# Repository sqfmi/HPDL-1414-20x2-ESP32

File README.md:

# HPDL-1414-20x2-ESP32
- 20x2 Character Display with HPDL1414 modules &amp; ESP32
- PCB Structure
- Arduino Library 👉 https://github.com/sqfmi/HPDL1414-74HC595-Arduino
- OSHWA Certified [**US000625**](https://certification.oshwa.org/us000625.html)

## Bill of Materials
| Component           | Quantity | Link                                             |
|---------------------|----------|--------------------------------------------------|
| HPDL1414            | 10       | https://www.aliexpress.com/item/32604004029.html |
| ESP32-WROOM-32D     | 1        |                                                  |
| CP2104              | 1        |                                                  |
| AMS1117-3.3V        | 1        |                                                  |
| 74HC595 SOIC-16     | 3        |                                                  |
| 0.1uF 0805          | 15       |                                                  |
| 4.7uF 0805          | 1        |                                                  |
| 10uF 0805           | 1        |                                                  |
| Micro USB Connector | 1        |                                                  |
| S8050 SOT-23        | 2        |                                                  |
| 10K 0805            | 4        |                                                  |

## License
Designed by SQFMI. Creative Commons Attribution/Share-Alike. See LICENSE for additional information.

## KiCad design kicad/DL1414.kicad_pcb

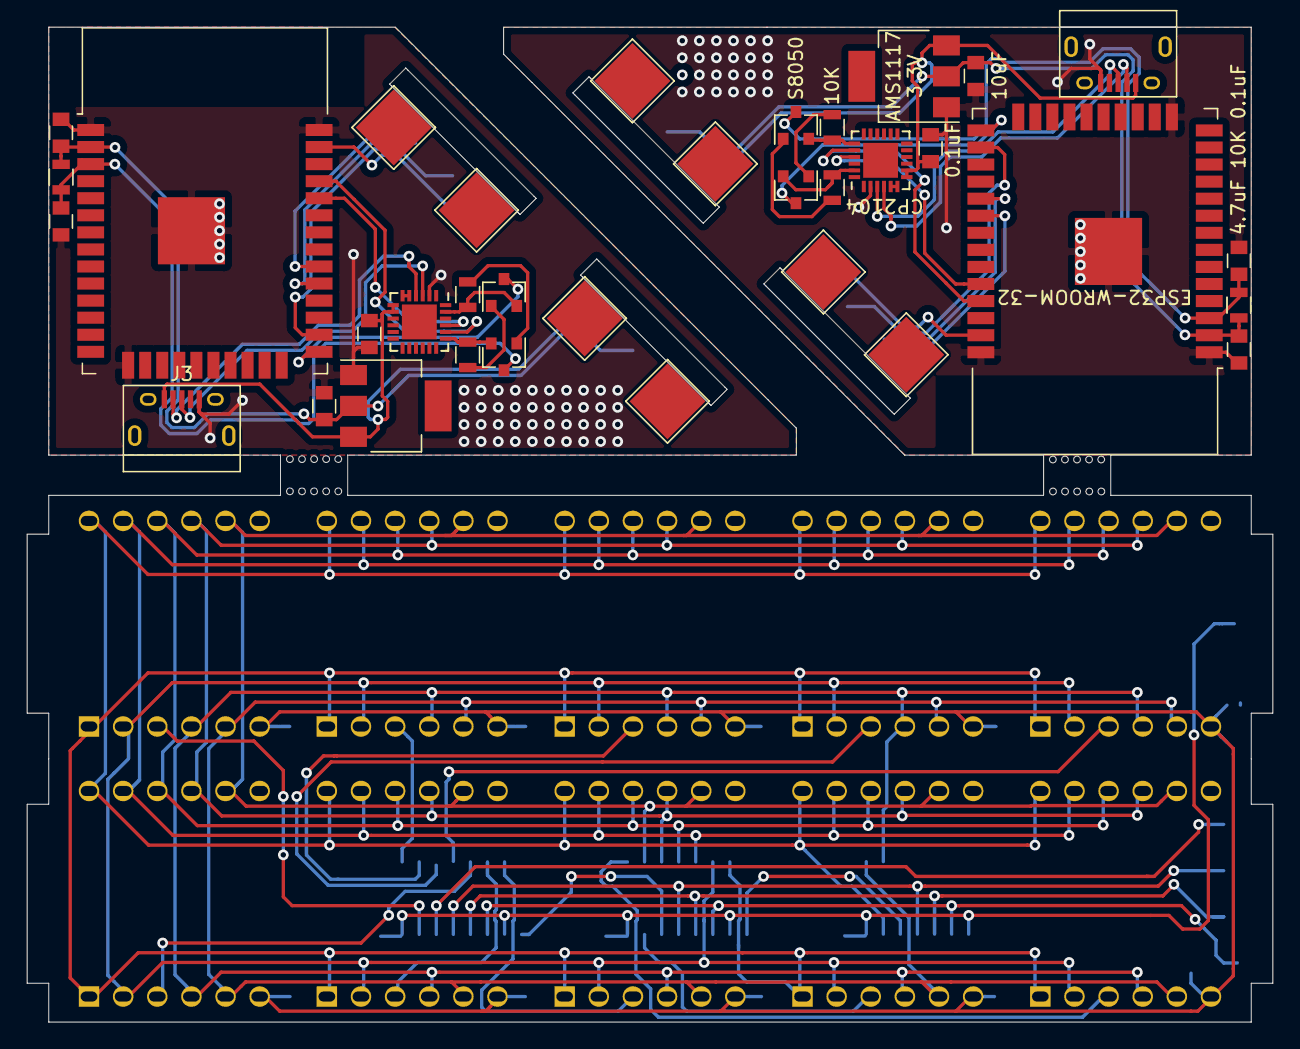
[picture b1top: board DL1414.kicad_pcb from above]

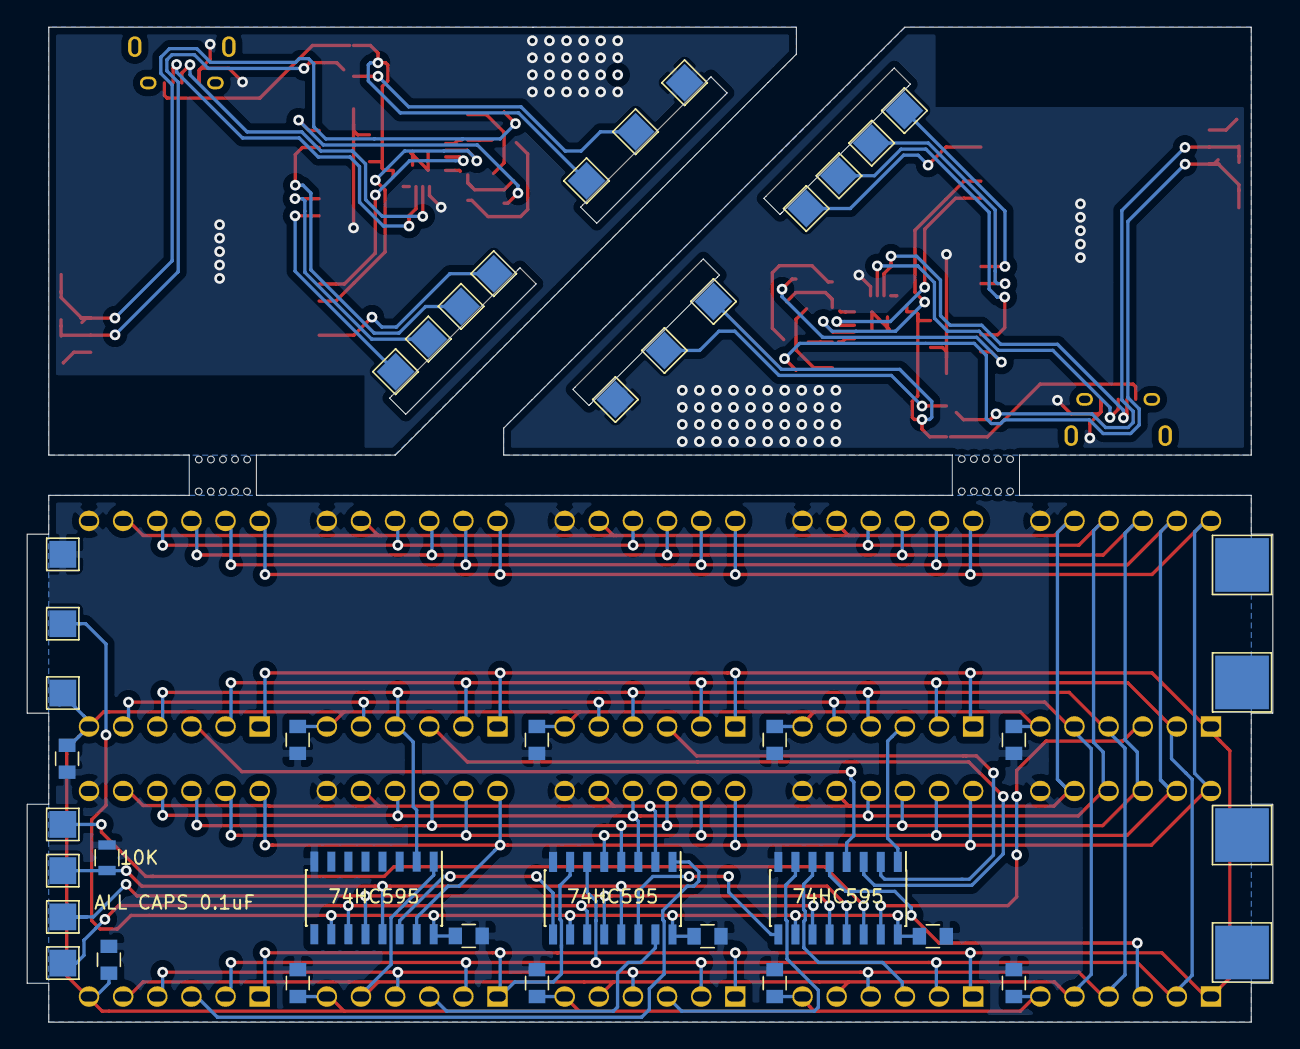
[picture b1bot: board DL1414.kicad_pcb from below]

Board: 2 copper layers, 92.7 x 74.0 mm, 86 parts (42 on the bottom side), 84 nets.

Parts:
C1, C2, C3, C4, C5, C6, C7, C8, C9, C10, C12, C12#2, C13, C13#2, C14, C15, C16: 0.1uF; C_0805
C11, C11#2: 4.7uF; C_0805
C17, C17#2: 10uF; C_0805
J3, J3#2: USB_B_Micro; USB_Micro-B
Q1, Q1#2, Q2, Q2#2: S8050; SOT-23
R1, R2, R2#2, R3, R3#2, R4, R4#2: 10K; R_0805
TP1, TP2, TP2#2, TP3, TP4, TP4#2, TP5, TP6, TP6#2, TP7, TP8, TP8#2, TP9, TP10, TP10#2, TP11, TP12, TP12#2, TP13, TP14, TP14#2: TestPoint; TestPoint_Pad_2.0x2.0mm
TP15, TP16, TP16#2, TP17, TP18, TP18#2, TP19, TP20, TP20#2, TP21, TP22, TP22#2: Mount Point; TestPoint_Pad_4.0x4.0mm
U1, U2, U3, U4, U5, U6, U7, U8, U9, U10: HPDL1414; HPDLDL-1414
U11, U12, U13: 74HC595; SOIC-16_3.9x9.9mm_Pitch1.27mm
U14, U14#2: CP2104; QFN-24-1EP_4x4mm_Pitch0.5mm
U15, U15#2: ESP32-WROOM-32D; ESP32-WROOM-32
U16, U16#2: AMS1117-3.3; SOT-223

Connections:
+3V3: C11.2, C11#2.2, C14.1, C15.1, C16.1, C17.1, C17#2.1, R2.1, R2#2.1, TP3.1, TP4.1, TP4#2.1, U11.10, U11.16, U12.10, U12.16, U13.10, U13.16, U15.2, U15#2.2, U16.2, U16#2.2
+5V: C1.1, C2.1, C3.1, C4.1, C5.1, C6.1, C7.1, C8.1, C9.1, C10.1, C13.2, C13#2.2, J3.1, J3#2.1, TP1.1, TP2.1, TP2#2.1, U1.6, U2.6, U3.6, U4.6, U5.6, U6.6, U7.6, U8.6, U9.6, U10.6, U14.7, U14.8, U14#2.7, U14#2.8, U16.3, U16#2.3
A0: U1.5, U2.5, U3.5, U4.5, U5.5, U6.5, U7.5, U8.5, U9.5, U10.5, U13.1
A1: U1.4, U2.4, U3.4, U4.4, U5.4, U6.4, U7.4, U8.4, U9.4, U10.4, U13.2
D0: U1.8, U2.8, U3.8, U4.8, U5.8, U6.8, U7.8, U8.8, U9.8, U10.8, U12.2
D1: U1.9, U2.9, U3.9, U4.9, U5.9, U6.9, U7.9, U8.9, U9.9, U10.9, U12.3
D2: U1.10, U2.10, U3.10, U4.10, U5.10, U6.10, U7.10, U8.10, U9.10, U10.10, U12.4
D3: U1.11, U2.11, U3.11, U4.11, U5.11, U6.11, U7.11, U8.11, U9.11, U10.11, U12.5
D4: U1.2, U2.2, U3.2, U4.2, U5.2, U6.2, U7.2, U8.2, U9.2, U10.2, U12.6
D5: U1.1, U2.1, U3.1, U4.1, U5.1, U6.1, U7.1, U8.1, U9.1, U10.1, U12.7
D6: U1.12, U2.12, U3.12, U4.12, U5.12, U6.12, U7.12, U8.12, U9.12, U10.12, U13.15
DTR: Q2.2, Q2#2.2, R3.2, R3#2.2, U14.23, U14#2.23
EN: C12.1, C12#2.1, Q1.3, Q1#2.3, R2.2, R2#2.2, U15.3, U15#2.3
GND: C1.2, C2.2, C3.2, C4.2, C5.2, C6.2, C7.2, C8.2, C9.2, C10.2, C11.1, C11#2.1, C12.2, C12#2.2, C13.1, C13#2.1, C14.2, C15.2, C16.2, C17.2, C17#2.2, J3.5, J3#2.5, R1.2, TP5.1, TP6.1, TP6#2.1, U1.7, U2.7, U3.7, U4.7, U5.7, U6.7, U7.7, U8.7, U9.7, U10.7, U11.8, U12.8, U13.8, U14.2, U14#2.2, U15.1, U15.15, U15.38, U15.39, U15#2.1, U15#2.15, U15#2.38, U15#2.39, U16.1, U16#2.1
IO0: Q2.3, Q2#2.3, U15.25, U15#2.25
LATCH: TP11.1, TP12.1, TP12#2.1, U11.12, U12.12, U13.12, U15.29, U15#2.29
unnamed: J3.2, J3#2.2, U14.4, U14#2.4
unnamed: J3.3, J3#2.3, U14.3, U14#2.3
unnamed: J3.4, J3#2.4
unnamed: Q1.1, Q1#2.1, R3.1, R3#2.1
unnamed: Q2.1, Q2#2.1, R4.1, R4#2.1
unnamed: TP16.1, TP16#2.1
unnamed: TP18.1, TP18#2.1
unnamed: TP20.1, TP20#2.1
unnamed: TP22.1, TP22#2.1
unnamed: U11.9, U12.14
unnamed: U12.9, U13.14
unnamed: U14.1, U14#2.1
unnamed: U14.5, U14.6, U14#2.5, U14#2.6
unnamed: U14.9, U14#2.9
unnamed: U14.10, U14#2.10
unnamed: U14.11, U14#2.11
unnamed: U14.12, U14#2.12
unnamed: U14.13, U14#2.13
unnamed: U14.14, U14#2.14
unnamed: U14.15, U14#2.15
unnamed: U14.16, U14#2.16
unnamed: U14.17, U14#2.17
unnamed: U14.18, U14#2.18
unnamed: U14.22, U14#2.22
unnamed: U14.24, U14#2.24
unnamed: U14.25, U14#2.25
unnamed: U15.4, U15#2.4
unnamed: U15.5, U15#2.5
unnamed: U15.6, U15#2.6
unnamed: U15.7, U15#2.7
unnamed: U15.8, U15#2.8
unnamed: U15.9, U15#2.9
unnamed: U15.10, U15#2.10
unnamed: U15.11, U15#2.11
unnamed: U15.12, U15#2.12
unnamed: U15.13, U15#2.13
unnamed: U15.14, U15#2.14
unnamed: U15.16, U15#2.16
unnamed: U15.17, U15#2.17
unnamed: U15.18, U15#2.18
unnamed: U15.19, U15#2.19
unnamed: U15.20, U15#2.20
unnamed: U15.21, U15#2.21
unnamed: U15.22, U15#2.22
unnamed: U15.23, U15#2.23
unnamed: U15.24, U15#2.24
unnamed: U15.27, U15#2.27
unnamed: U15.28, U15#2.28
unnamed: U15.31, U15#2.31
unnamed: U15.32, U15#2.32
unnamed: U15.33, U15#2.33
unnamed: U15.36, U15#2.36
OE: R1.1, TP13.1, TP14.1, TP14#2.1, U11.13, U12.13, U13.13, U15.26, U15#2.26
RTS: Q1.2, Q1#2.2, R4.2, R4#2.2, U14.19, U14#2.19
RX: U14.21, U14#2.21, U15.34, U15#2.34
SCL: TP9.1, TP10.1, TP10#2.1, U11.11, U12.11, U13.11, U15.30, U15#2.30
SDA: TP7.1, TP8.1, TP8#2.1, U11.14, U15.37, U15#2.37
TX: U14.20, U14#2.20, U15.35, U15#2.35
WR0: U1.3, U11.15
WR1: U2.3, U11.1
WR2: U3.3, U11.2
WR3: U4.3, U11.3
WR4: U5.3, U11.4
WR5: U6.3, U11.5
WR6: U7.3, U11.6
WR7: U8.3, U11.7
WR8: U9.3, U12.15
WR9: U10.3, U12.1

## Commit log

2020-05-06 Create pic
2020-05-23 Create LICENSE
2020-05-23 Update LICENSE
